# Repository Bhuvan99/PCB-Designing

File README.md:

# PCB-Designing
It contains the PCB circuits that have been designed by making use of different Datasheets.

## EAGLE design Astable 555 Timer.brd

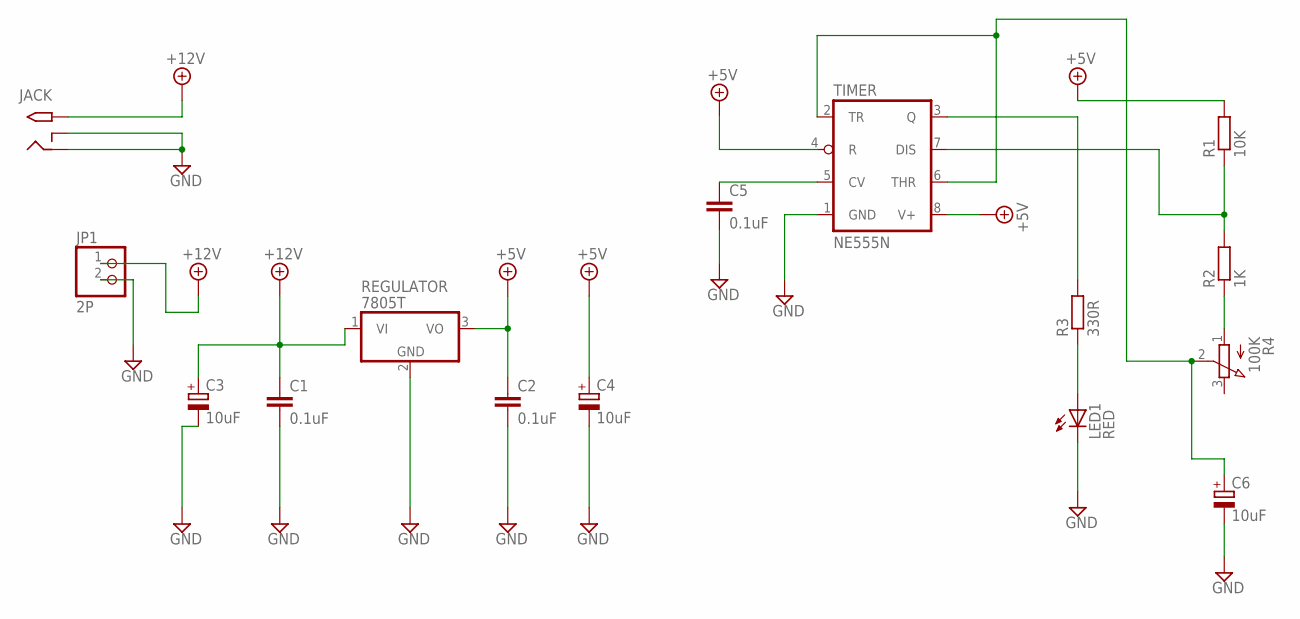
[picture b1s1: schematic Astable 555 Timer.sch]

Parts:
C1, C2, C5: 0.1uF; C050-035X075
C3, C4, C6: 10uF; E3,5-8
JACK: 2.1MMJACKTHM; PJ-102A
JP1: 2P; 1X02
LED1: RED; LED5MM
R1: 10K; 0207/15
R2: 1K; 0207/15
R3: 330R; 0207/15
R4: 100K; 3RP/1610N
REGULATOR: 7805T; TO220H
TIMER: NE555N; DIL08-ROUND

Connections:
+5V: C2.1, C4.+, R1.2, REGULATOR.3 (VO), TIMER.4 (R), TIMER.8 (V+)
+12V: C1.1, C3.+, JACK.TIP, JP1.1, REGULATOR.1 (VI)
GND: C1.2, C2.2, C3.-, C4.-, C5.2, C6.-, JACK.RING, JACK.RING_SW, JP1.2, LED1.K (C), REGULATOR.2 (GND), TIMER.1 (GND)
unnamed: C5.1, TIMER.5 (CV)
unnamed: R1.1, R2.2, TIMER.7 (DIS)
unnamed: C6.+, R4.2 (S), TIMER.2 (TR), TIMER.6 (THR)
unnamed: R3.2, TIMER.3 (Q)
unnamed: LED1.A, R3.1
unnamed: R2.1, R4.1 (A)

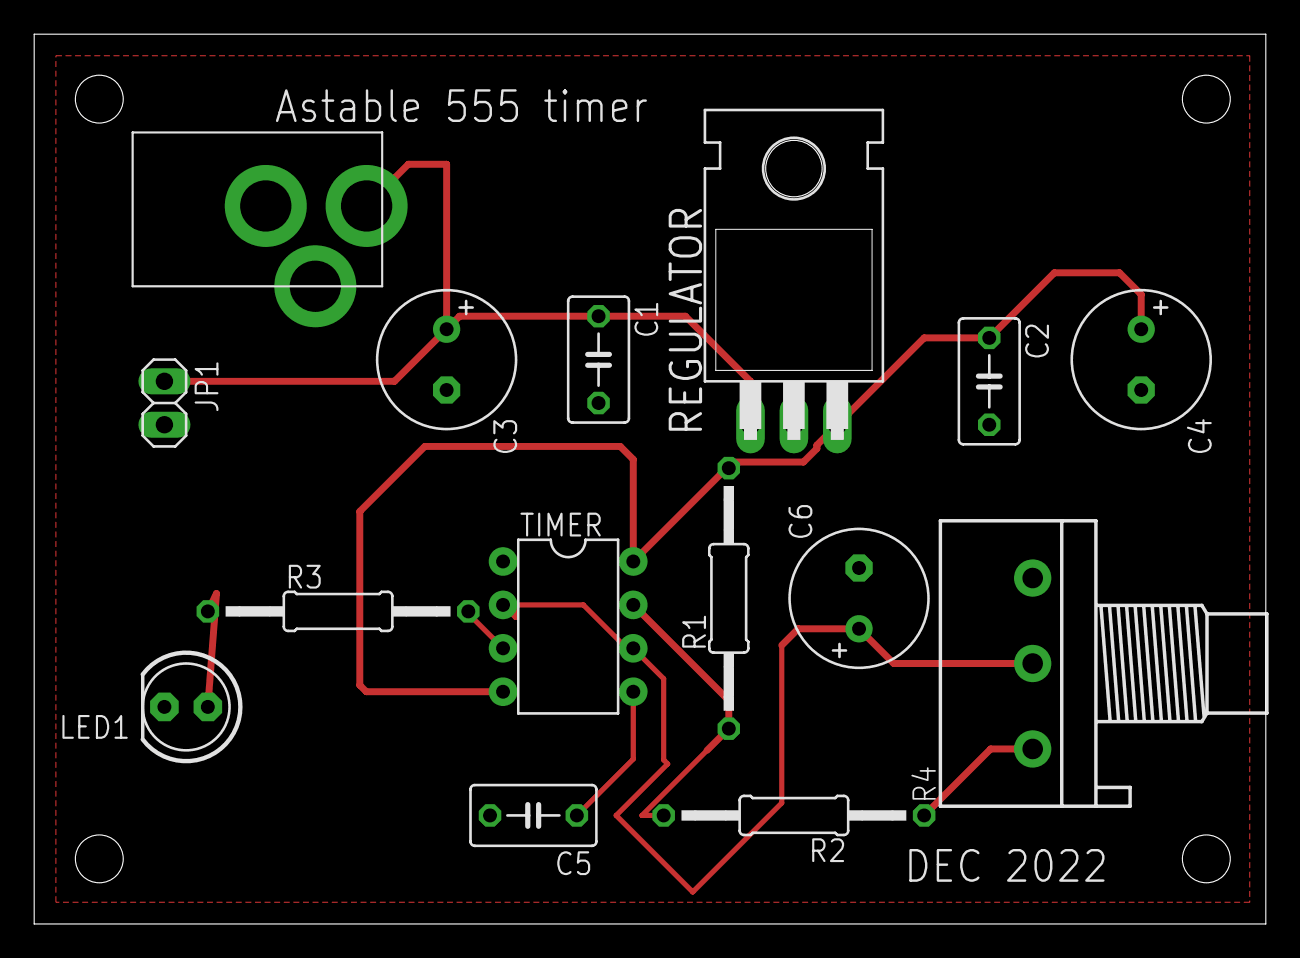
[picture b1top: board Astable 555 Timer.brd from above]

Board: 2 copper layers, 72.1 x 52.1 mm, 15 parts (0 on the bottom side), 9 nets.

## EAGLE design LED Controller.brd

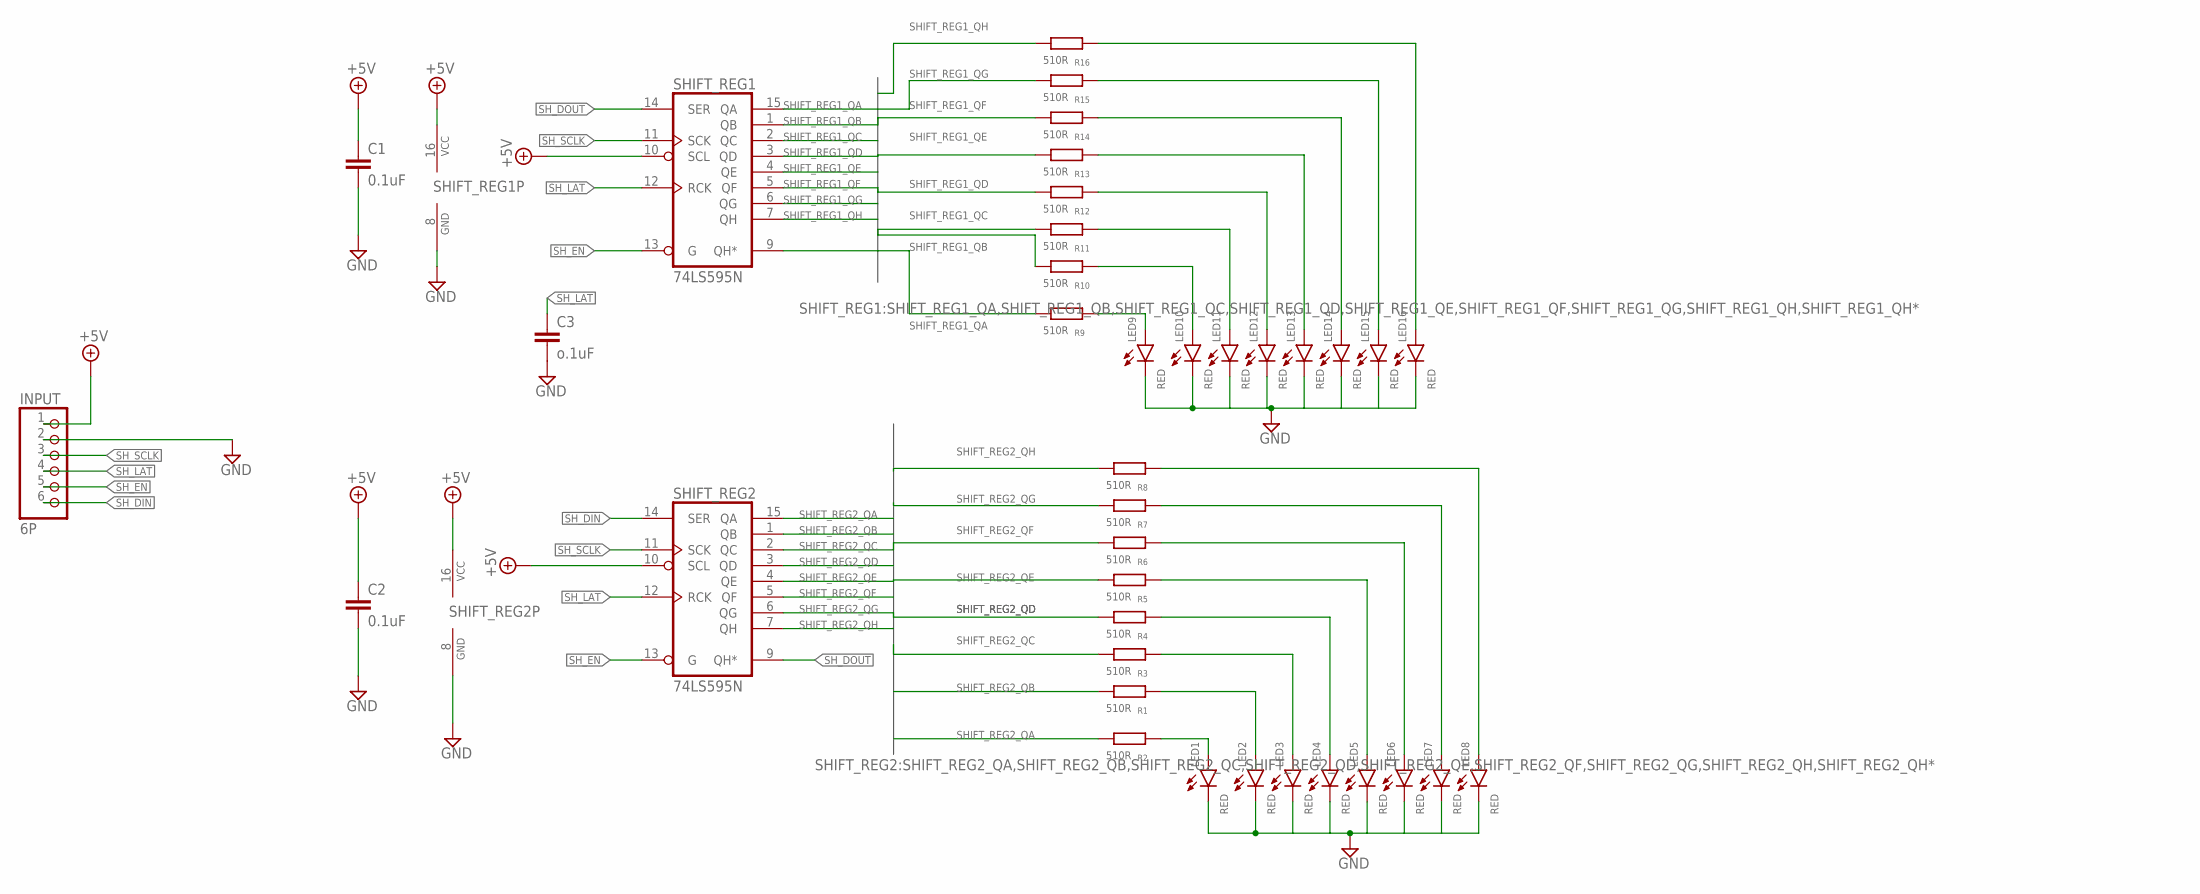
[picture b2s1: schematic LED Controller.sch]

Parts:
C1, C2: 0.1uF; C050-030X075
C3: o.1uF; C050-030X075
INPUT: 6P; 1X06/90
LED1, LED2, LED3, LED4, LED5, LED6, LED7, LED8, LED9, LED10, LED11, LED12, LED13, LED14, LED15, LED16: RED; LED5MM
R1, R2, R3, R4, R5, R6, R7, R8, R9, R10, R11, R12, R13, R14, R15, R16: 510R; 0207/10
SHIFT_REG1, SHIFT_REG2: 74LS595N; DIL16

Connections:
+5V: C1.1, C2.1, INPUT.1, SHIFT_REG1.10 (SCL), SHIFT_REG1.16 (VCC), SHIFT_REG2.10 (SCL), SHIFT_REG2.16 (VCC)
GND: C1.2, C2.2, C3.2, INPUT.2, LED1.K (C), LED2.K (C), LED3.K (C), LED4.K (C), LED5.K (C), LED6.K (C), LED7.K (C), LED8.K (C), LED9.K (C), LED10.K (C), LED11.K (C), LED12.K (C), LED13.K (C), LED14.K (C), LED15.K (C), LED16.K (C), SHIFT_REG1.8 (GND), SHIFT_REG2.8 (GND)
unnamed: LED9.A, R9.2
unnamed: LED10.A, R10.2
unnamed: LED11.A, R11.2
unnamed: LED12.A, R12.2
unnamed: LED13.A, R13.2
unnamed: LED14.A, R14.2
unnamed: LED15.A, R15.2
unnamed: LED16.A, R16.2
unnamed: LED1.A, R2.2
unnamed: LED2.A, R1.2
unnamed: LED3.A, R3.2
unnamed: LED4.A, R4.2
unnamed: LED5.A, R5.2
unnamed: LED6.A, R6.2
unnamed: LED7.A, R7.2
unnamed: LED8.A, R8.2
SHIFT_REG1_QA: R9.1, SHIFT_REG1.15 (QA)
SHIFT_REG1_QB: R10.1, SHIFT_REG1.1 (QB)
SHIFT_REG1_QC: R11.1, SHIFT_REG1.2 (QC)
SHIFT_REG1_QD: R12.1, SHIFT_REG1.3 (QD)
SHIFT_REG1_QE: R13.1, SHIFT_REG1.4 (QE)
SHIFT_REG1_QF: R14.1, SHIFT_REG1.5 (QF)
SHIFT_REG1_QG: R15.1, SHIFT_REG1.6 (QG)
SHIFT_REG1_QH: R16.1, SHIFT_REG1.7 (QH)
SHIFT_REG1_QH*: SHIFT_REG1.9 (QH*)
SHIFT_REG2_QA: R2.1, SHIFT_REG2.15 (QA)
SHIFT_REG2_QB: R1.1, SHIFT_REG2.1 (QB)
SHIFT_REG2_QC: R3.1, SHIFT_REG2.2 (QC)
SHIFT_REG2_QD: R4.1, SHIFT_REG2.3 (QD)
SHIFT_REG2_QE: R5.1, SHIFT_REG2.4 (QE)
SHIFT_REG2_QF: R6.1, SHIFT_REG2.5 (QF)
SHIFT_REG2_QG: R7.1, SHIFT_REG2.6 (QG)
SHIFT_REG2_QH: R8.1, SHIFT_REG2.7 (QH)
SH_DIN: INPUT.6, SHIFT_REG2.14 (SER)
SH_DOUT: SHIFT_REG1.14 (SER), SHIFT_REG2.9 (QH*)
SH_EN: INPUT.5, SHIFT_REG1.13 (G), SHIFT_REG2.13 (G)
SH_LAT: C3.1, INPUT.4, SHIFT_REG1.12 (RCK), SHIFT_REG2.12 (RCK)
SH_SCLK: INPUT.3, SHIFT_REG1.11 (SCK), SHIFT_REG2.11 (SCK)

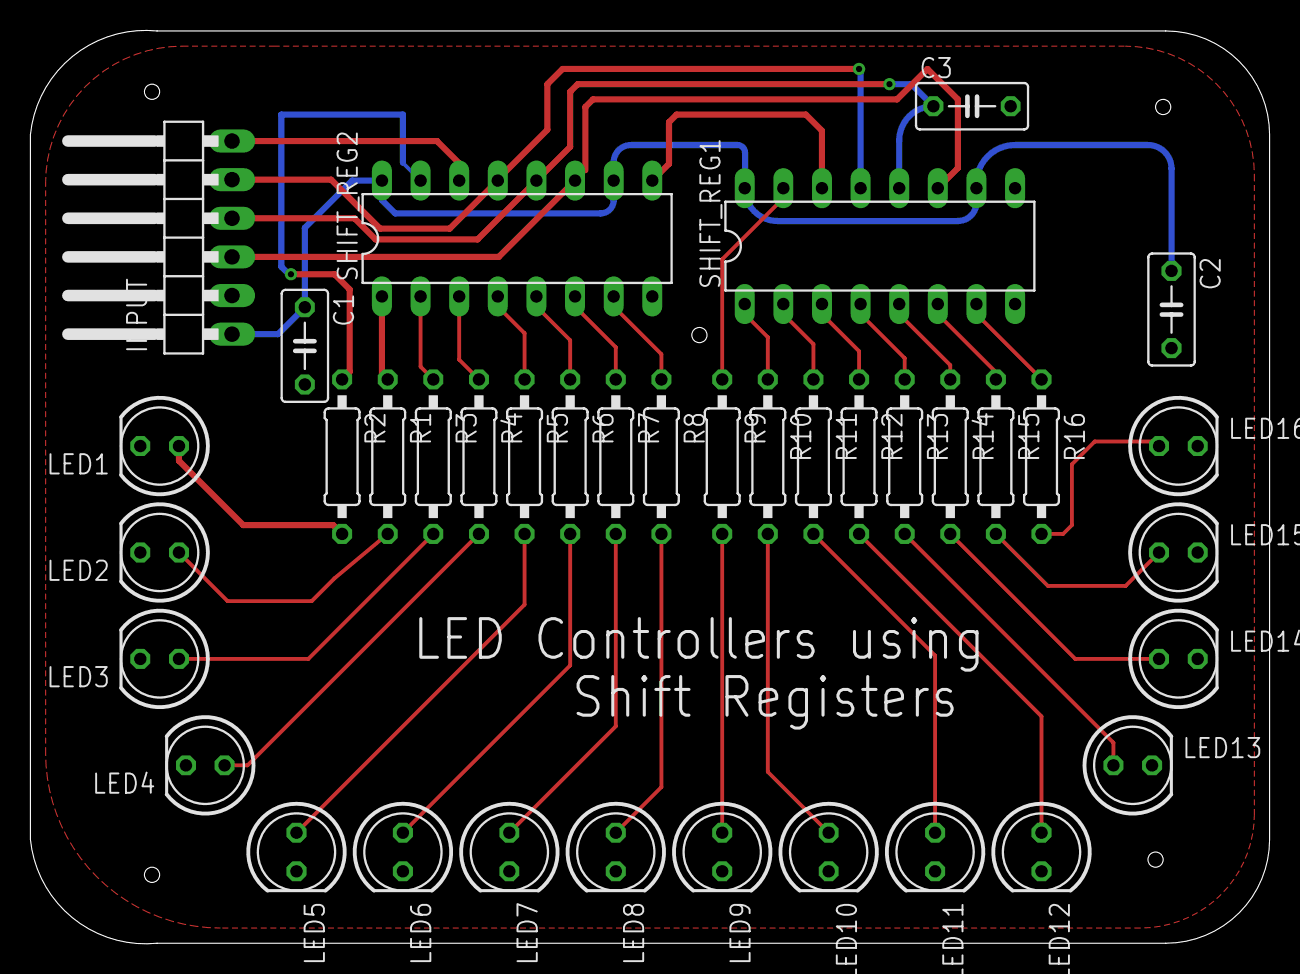
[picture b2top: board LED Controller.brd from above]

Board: 2 copper layers, 81.5 x 60.1 mm, 38 parts (0 on the bottom side), 39 nets.
